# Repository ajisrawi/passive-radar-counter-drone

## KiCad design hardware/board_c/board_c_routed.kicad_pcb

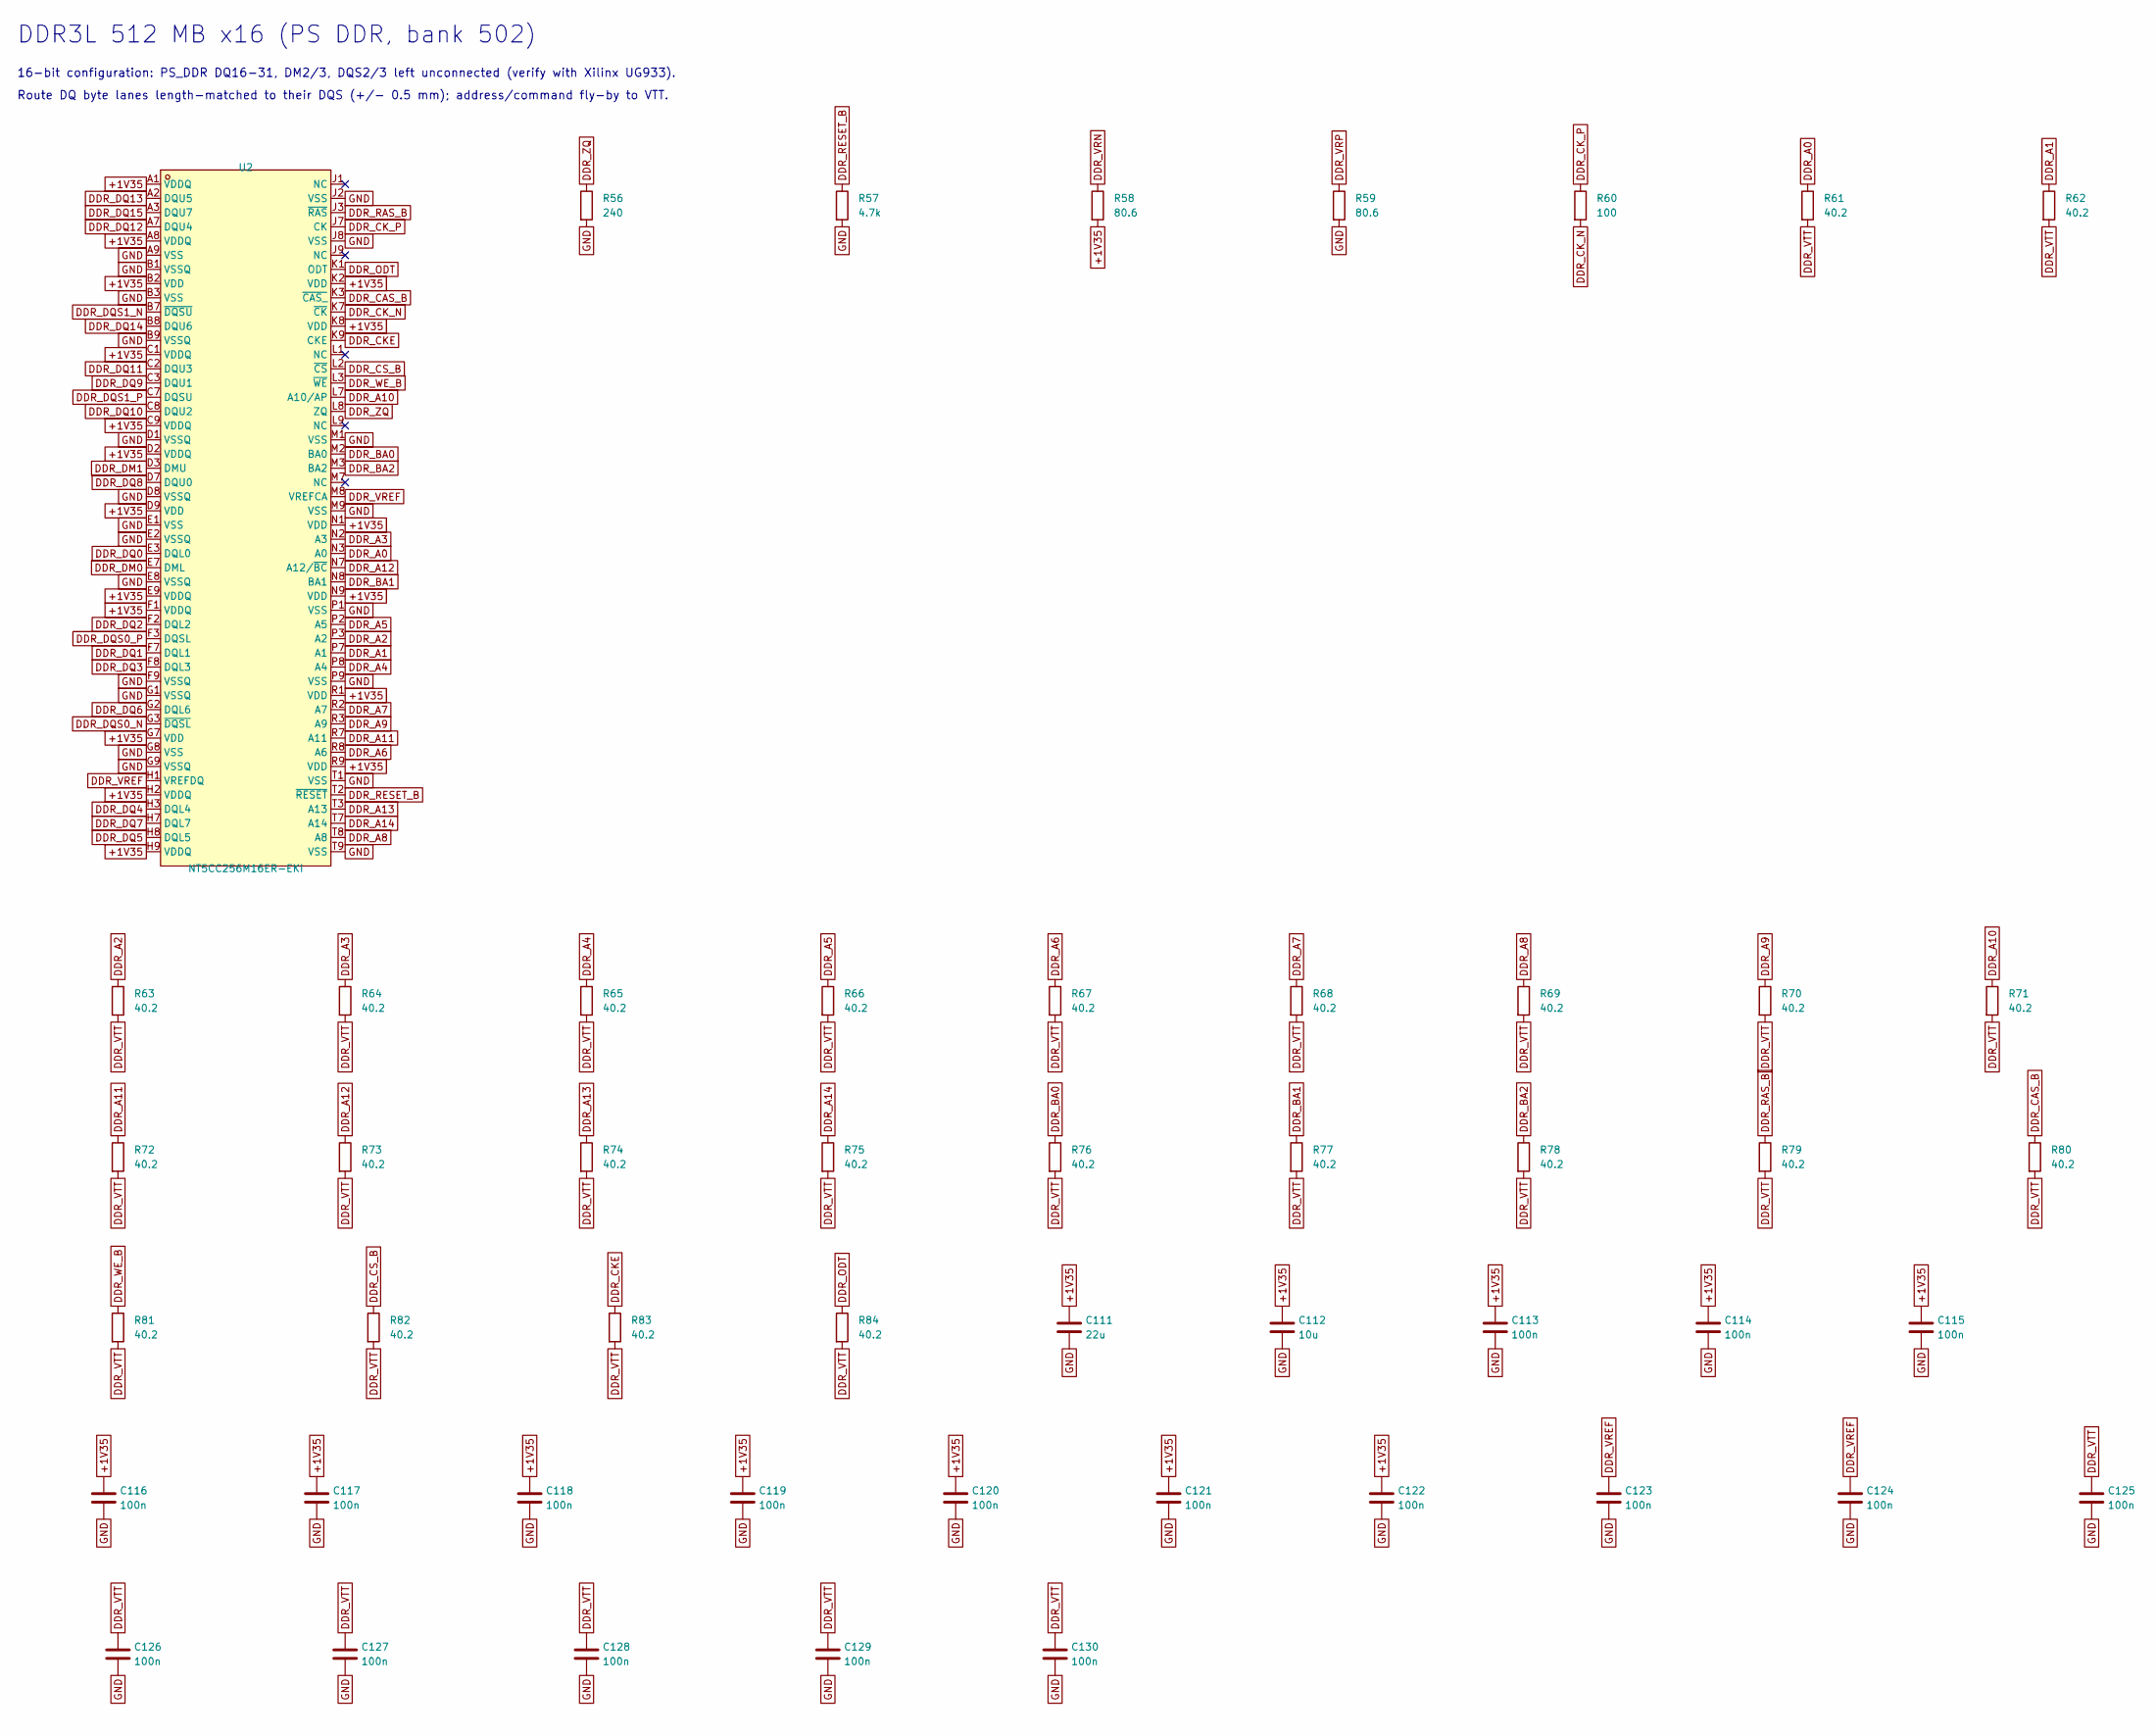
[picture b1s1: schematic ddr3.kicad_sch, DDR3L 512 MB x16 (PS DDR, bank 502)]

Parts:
C111: 22u; C_0805_2012Metric; LCSC C45783
C112: 10u; C_0603_1608Metric; LCSC C19702
C113, C114, C115, C116, C117, C118, C119, C120, C121, C122, C123, C124, C125, C126, C127, C128, C129, C130: 100n; C_0402_1005Metric; LCSC C1525
R56: 240; R_0402_1005Metric; Tolerance 1%
R57: 4.7k; R_0402_1005Metric; LCSC C25900
R58, R59: 80.6; R_0402_1005Metric; Tolerance 1%
R60: 100; R_0402_1005Metric
R61, R62, R63, R64, R65, R66, R67, R68, R69, R70, R71, R72, R73, R74, R75, R76, R77, R78, R79, R80, R81, R82, R83, R84: 40.2; R_0402_1005Metric
U2: NT5CC256M16ER-EKI; TFBGA-96_L13.0-W8.0-R16-C6-P0.80-TL; MPN NT5CC256M16ER-EKI; LCSC C2841153

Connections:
+1V35: C111.1, C112.1, C113.1, C114.1, C115.1, C116.1, C117.1, C118.1, C119.1, C120.1, C121.1, C122.1, R58.2, U2.A1 (VDDQ), U2.A8 (VDDQ), U2.B2 (VDD), U2.C1 (VDDQ), U2.C9 (VDDQ), U2.D2 (VDDQ), U2.D9 (VDD), U2.E9 (VDDQ), U2.F1 (VDDQ), U2.G7 (VDD), U2.H2 (VDDQ), U2.H9 (VDDQ), U2.K2 (VDD), U2.K8 (VDD), U2.N1 (VDD), U2.N9 (VDD), U2.R1 (VDD), U2.R9 (VDD); also elsewhere on the board
DDR_A0: R61.1, U2.N3 (A0); also elsewhere on the board
DDR_A1: R62.1, U2.P7 (A1); also elsewhere on the board
DDR_A2: R63.1, U2.P3 (A2); also elsewhere on the board
DDR_A3: R64.1, U2.N2 (A3); also elsewhere on the board
DDR_A4: R65.1, U2.P8 (A4); also elsewhere on the board
DDR_A5: R66.1, U2.P2 (A5); also elsewhere on the board
DDR_A6: R67.1, U2.R8 (A6); also elsewhere on the board
DDR_A7: R68.1, U2.R2 (A7); also elsewhere on the board
DDR_A8: R69.1, U2.T8 (A8); also elsewhere on the board
DDR_A9: R70.1, U2.R3 (A9); also elsewhere on the board
DDR_A10: R71.1, U2.L7 (A10/AP); also elsewhere on the board
DDR_A11: R72.1, U2.R7 (A11); also elsewhere on the board
DDR_A12: R73.1, U2.N7 (A12/~BC); also elsewhere on the board
DDR_A13: R74.1, U2.T3 (A13); also elsewhere on the board
DDR_A14: R75.1, U2.T7 (A14); also elsewhere on the board
DDR_BA0: R76.1, U2.M2 (BA0); also elsewhere on the board
DDR_BA1: R77.1, U2.N8 (BA1); also elsewhere on the board
DDR_BA2: R78.1, U2.M3 (BA2); also elsewhere on the board
DDR_CAS_B: R80.1, U2.K3 (~CAS_); also elsewhere on the board
DDR_CKE: R83.1, U2.K9 (CKE); also elsewhere on the board
DDR_CK_N: R60.2, U2.K7 (~CK); also elsewhere on the board
DDR_CK_P: R60.1, U2.J7 (CK); also elsewhere on the board
DDR_CS_B: R82.1, U2.L2 (~CS); also elsewhere on the board
DDR_DM0: U2.E7 (DML); also elsewhere on the board
DDR_DM1: U2.D3 (DMU); also elsewhere on the board
DDR_DQ0: U2.E3 (DQL0); also elsewhere on the board
DDR_DQ1: U2.F7 (DQL1); also elsewhere on the board
DDR_DQ2: U2.F2 (DQL2); also elsewhere on the board
DDR_DQ3: U2.F8 (DQL3); also elsewhere on the board
DDR_DQ4: U2.H3 (DQL4); also elsewhere on the board
DDR_DQ5: U2.H8 (DQL5); also elsewhere on the board
DDR_DQ6: U2.G2 (DQL6); also elsewhere on the board
DDR_DQ7: U2.H7 (DQL7); also elsewhere on the board
DDR_DQ8: U2.D7 (DQU0); also elsewhere on the board
DDR_DQ9: U2.C3 (DQU1); also elsewhere on the board
DDR_DQ10: U2.C8 (DQU2); also elsewhere on the board
DDR_DQ11: U2.C2 (DQU3); also elsewhere on the board
DDR_DQ12: U2.A7 (DQU4); also elsewhere on the board
DDR_DQ13: U2.A2 (DQU5); also elsewhere on the board
DDR_DQ14: U2.B8 (DQU6); also elsewhere on the board
DDR_DQ15: U2.A3 (DQU7); also elsewhere on the board
DDR_DQS0_N: U2.G3 (~DQSL); also elsewhere on the board
DDR_DQS0_P: U2.F3 (DQSL); also elsewhere on the board
DDR_DQS1_N: U2.B7 (~DQSU); also elsewhere on the board
DDR_DQS1_P: U2.C7 (DQSU); also elsewhere on the board
DDR_ODT: R84.1, U2.K1 (ODT); also elsewhere on the board
DDR_RAS_B: R79.1, U2.J3 (~RAS); also elsewhere on the board
DDR_RESET_B: R57.1, U2.T2 (~RESET); also elsewhere on the board
DDR_VREF: C123.1, C124.1, U2.H1 (VREFDQ), U2.M8 (VREFCA); also elsewhere on the board
DDR_VRN: R58.1; also elsewhere on the board
DDR_VRP: R59.1; also elsewhere on the board
DDR_VTT: C125.1, C126.1, C127.1, C128.1, C129.1, C130.1, R61.2, R62.2, R63.2, R64.2, R65.2, R66.2, R67.2, R68.2, R69.2, R70.2, R71.2, R72.2, R73.2, R74.2, R75.2, R76.2, R77.2, R78.2, R79.2, R80.2, R81.2, R82.2, R83.2, R84.2; also elsewhere on the board
DDR_WE_B: R81.1, U2.L3 (~WE); also elsewhere on the board
DDR_ZQ: R56.1, U2.L8 (ZQ)
GND: C111.2, C112.2, C113.2, C114.2, C115.2, C116.2, C117.2, C118.2, C119.2, C120.2, C121.2, C122.2, C123.2, C124.2, C125.2, C126.2, C127.2, C128.2, C129.2, C130.2, R56.2, R57.2, R59.2, U2.A9 (VSS), U2.B1 (VSSQ), U2.B3 (VSS), U2.B9 (VSSQ), U2.D1 (VSSQ), U2.D8 (VSSQ), U2.E1 (VSS), U2.E2 (VSSQ), U2.E8 (VSSQ), U2.F9 (VSSQ), U2.G1 (VSSQ), U2.G8 (VSS), U2.G9 (VSSQ), U2.J2 (VSS), U2.J8 (VSS), U2.M1 (VSS), U2.M9 (VSS), U2.P1 (VSS), U2.P9 (VSS), U2.T1 (VSS), U2.T9 (VSS); also elsewhere on the board

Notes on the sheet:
DDR3L 512 MB x16 (PS DDR, bank 502)
16-bit configuration: PS_DDR DQ16-31, DM2/3, DQS2/3 left unconnected (verify with Xilinx UG933).
Route DQ byte lanes length-matched to their DQS (+/- 0.5 mm); address/command fly-by to VTT.

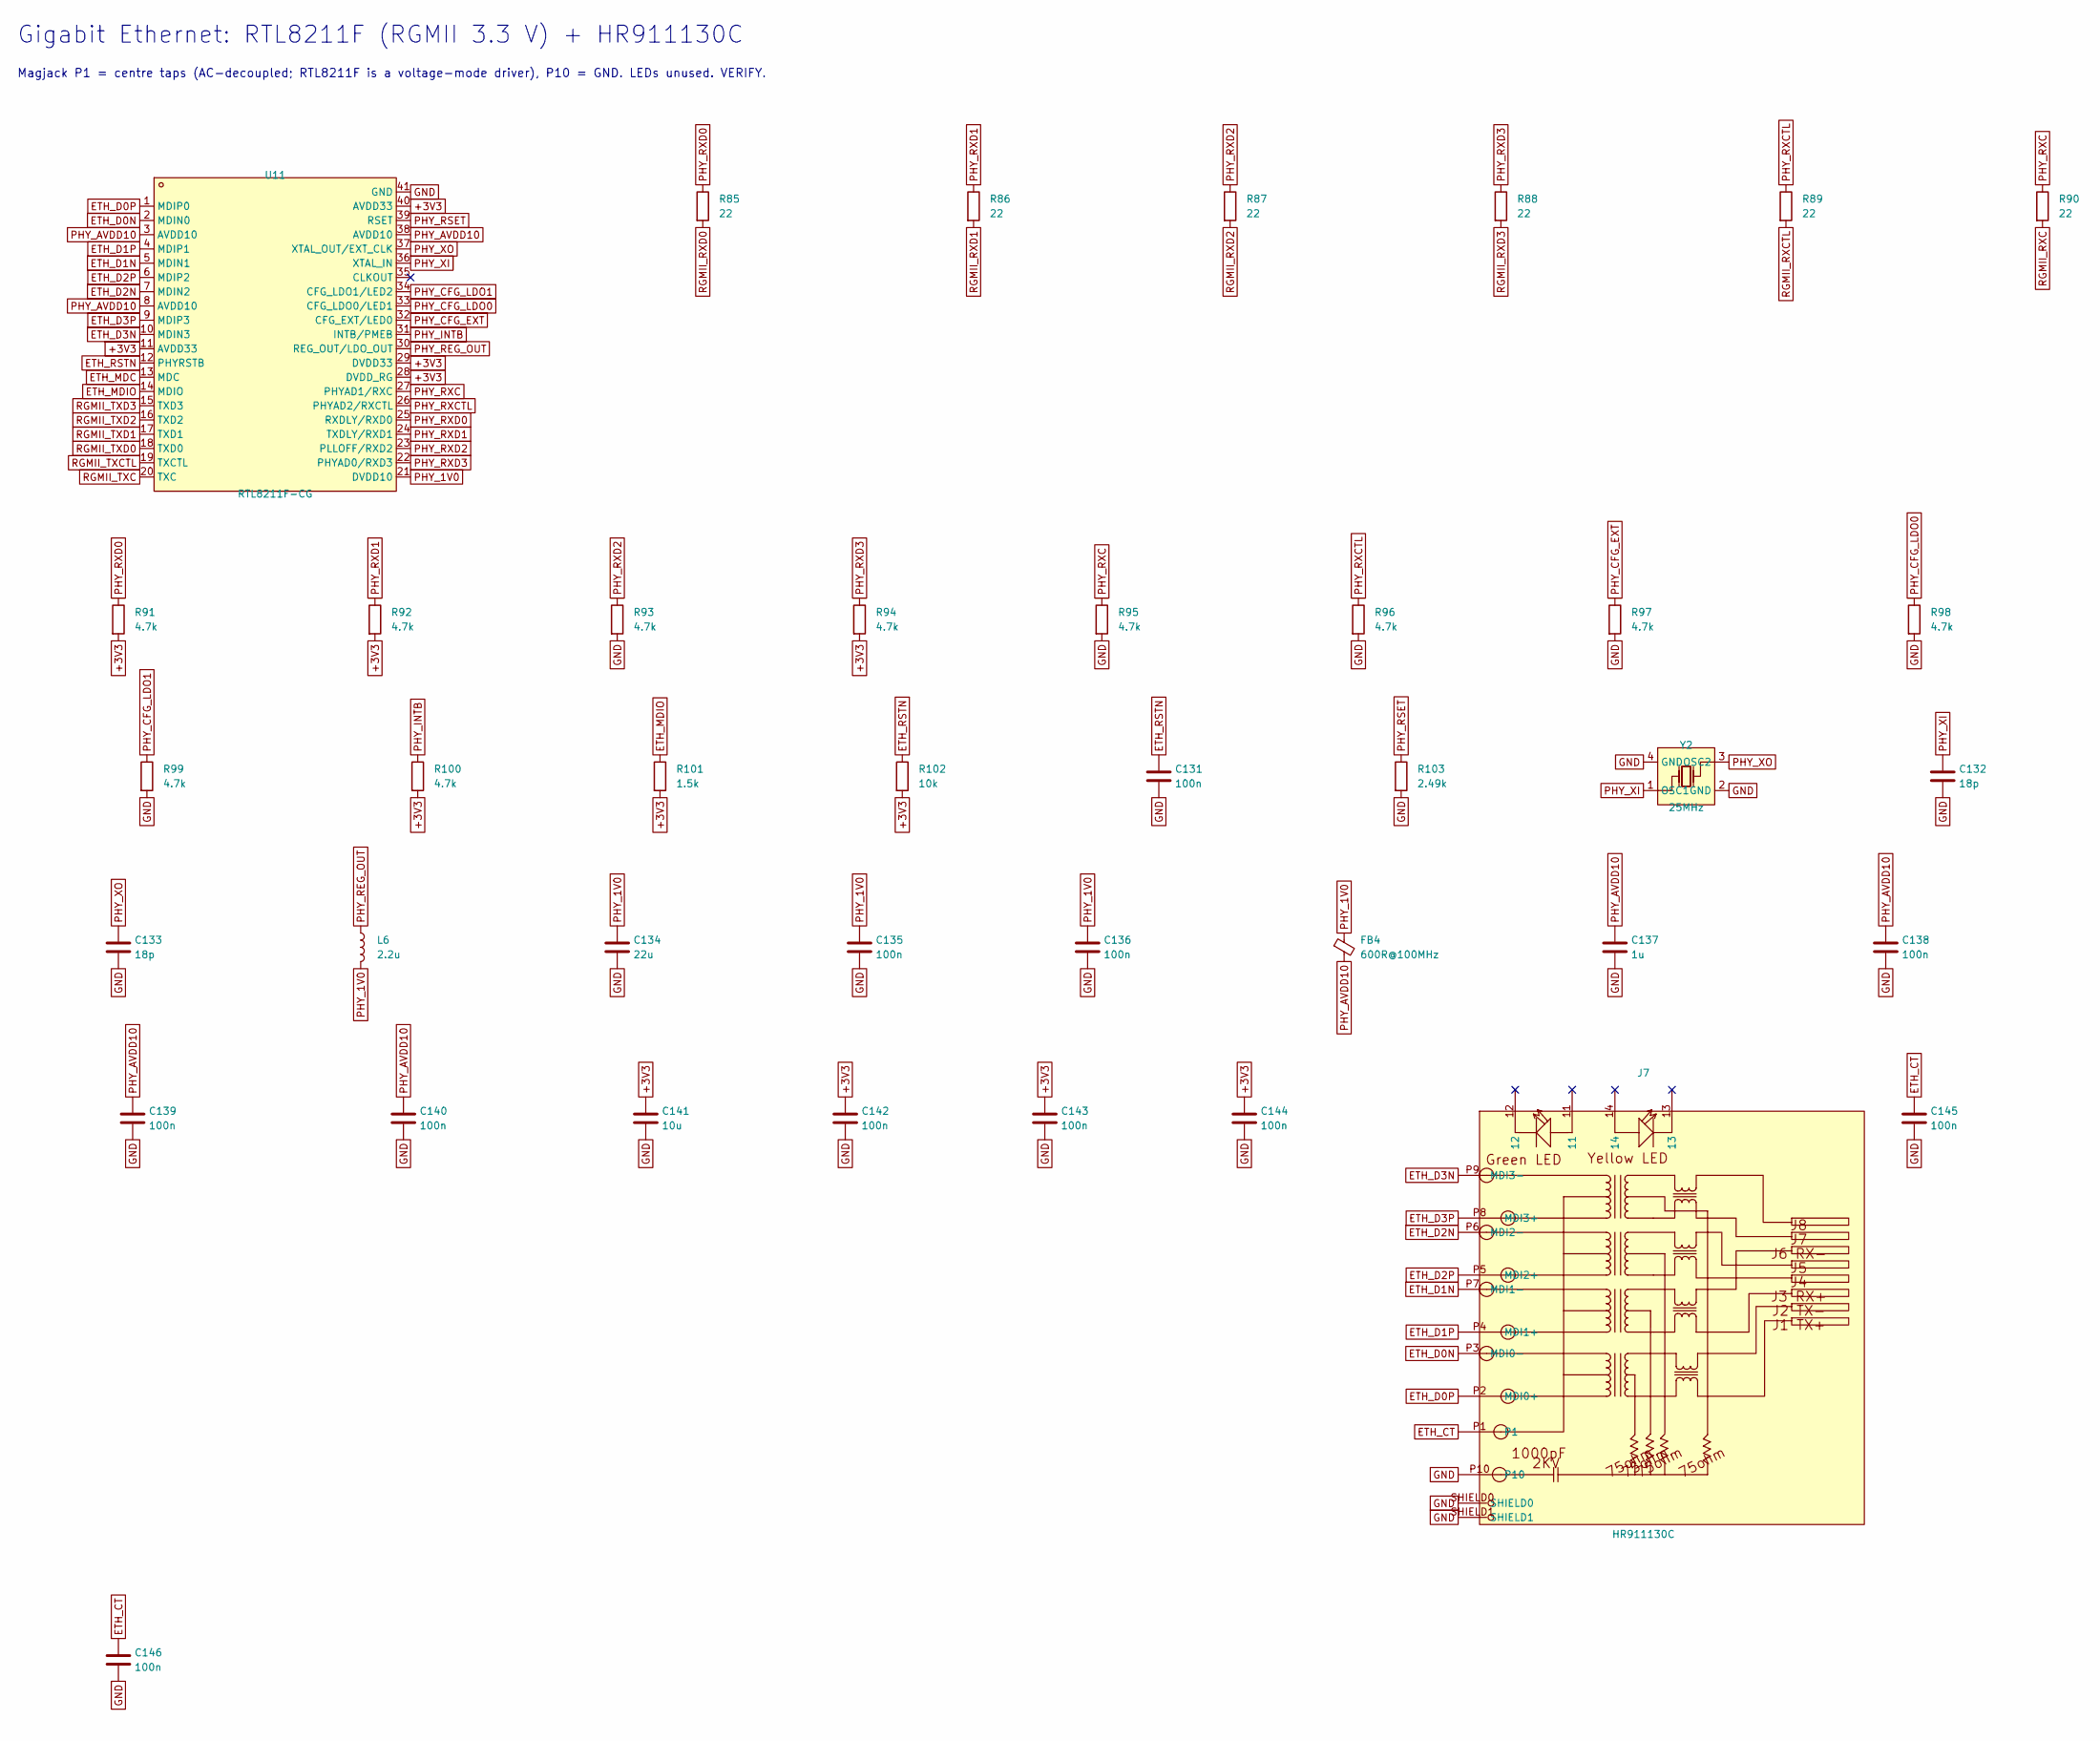
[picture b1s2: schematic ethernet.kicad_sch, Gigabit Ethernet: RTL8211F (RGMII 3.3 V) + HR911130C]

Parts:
C131, C135, C136, C138, C139, C140, C142, C143, C144, C145, C146: 100n; C_0402_1005Metric; LCSC C1525
C132, C133: 18p; C_0402_1005Metric
C134: 22u; C_0805_2012Metric; LCSC C45783
C137: 1u; C_0402_1005Metric; LCSC C52923
C141: 10u; C_0603_1608Metric; LCSC C19702
FB4: 600R@100MHz; L_0603_1608Metric
J7: HR911130C; RJ45-TH_HR911130C; MPN HR911130C; LCSC C50933
L6: 2.2u; L_0603_1608Metric
R85, R86, R87, R88, R89, R90: 22; R_0402_1005Metric
R91, R92, R93, R94, R95, R96, R97, R98, R99, R100: 4.7k; R_0402_1005Metric; LCSC C25900
R101: 1.5k; R_0402_1005Metric
R102: 10k; R_0402_1005Metric; LCSC C25744
R103: 2.49k; R_0402_1005Metric; Tolerance 1%
U11: RTL8211F-CG; WQFN-40_L5.0-W5.0-P0.4-BL-EP; MPN RTL8211F-CG; LCSC C187932
Y2: 25MHz; CRYSTAL-SMD_4P-L3.2-W2.5-BL; MPN X322525MOB4SI; LCSC C9006

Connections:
+3V3: C141.1, C142.1, C143.1, C144.1, R91.2, R92.2, R94.2, R100.2, R101.2, R102.2, U11.11 (AVDD33), U11.28 (DVDD_RG), U11.29 (DVDD33), U11.40 (AVDD33); also elsewhere on the board
ETH_CT: C145.1, C146.1, J7.P1
ETH_D0N: J7.P3 (MDI0-), U11.2 (MDIN0)
ETH_D0P: J7.P2 (MDI0+), U11.1 (MDIP0)
ETH_D1N: J7.P7 (MDI1-), U11.5 (MDIN1)
ETH_D1P: J7.P4 (MDI1+), U11.4 (MDIP1)
ETH_D2N: J7.P6 (MDI2-), U11.7 (MDIN2)
ETH_D2P: J7.P5 (MDI2+), U11.6 (MDIP2)
ETH_D3N: J7.P9 (MDI3-), U11.10 (MDIN3)
ETH_D3P: J7.P8 (MDI3+), U11.9 (MDIP3)
ETH_MDC: U11.13 (MDC); also elsewhere on the board
ETH_MDIO: R101.1, U11.14 (MDIO); also elsewhere on the board
ETH_RSTN: C131.1, R102.1, U11.12 (PHYRSTB); also elsewhere on the board
GND: C131.2, C132.2, C133.2, C134.2, C135.2, C136.2, C137.2, C138.2, C139.2, C140.2, C141.2, C142.2, C143.2, C144.2, C145.2, C146.2, J7.P10, J7.SHIELD0, J7.SHIELD1, R93.2, R95.2, R96.2, R97.2, R98.2, R99.2, R103.2, U11.41 (GND), Y2.2 (GND), Y2.4 (GND); also elsewhere on the board
PHY_1V0: C134.1, C135.1, C136.1, FB4.1, L6.2, U11.21 (DVDD10)
PHY_AVDD10: C137.1, C138.1, C139.1, C140.1, FB4.2, U11.3 (AVDD10), U11.8 (AVDD10), U11.38 (AVDD10)
PHY_CFG_EXT: R97.1, U11.32 (CFG_EXT/LED0)
PHY_CFG_LDO0: R98.1, U11.33 (CFG_LDO0/LED1)
PHY_CFG_LDO1: R99.1, U11.34 (CFG_LDO1/LED2)
PHY_INTB: R100.1, U11.31 (INTB/PMEB)
PHY_REG_OUT: L6.1, U11.30 (REG_OUT/LDO_OUT)
PHY_RSET: R103.1, U11.39 (RSET)
PHY_RXC: R90.1, R95.1, U11.27 (PHYAD1/RXC)
PHY_RXCTL: R89.1, R96.1, U11.26 (PHYAD2/RXCTL)
PHY_RXD0: R85.1, R91.1, U11.25 (RXDLY/RXD0)
PHY_RXD1: R86.1, R92.1, U11.24 (TXDLY/RXD1)
PHY_RXD2: R87.1, R93.1, U11.23 (PLLOFF/RXD2)
PHY_RXD3: R88.1, R94.1, U11.22 (PHYAD0/RXD3)
PHY_XI: C132.1, U11.36 (XTAL_IN), Y2.1 (OSC1)
PHY_XO: C133.1, U11.37 (XTAL_OUT/EXT_CLK), Y2.3 (OSC2)
RGMII_RXC: R90.2; also elsewhere on the board
RGMII_RXCTL: R89.2; also elsewhere on the board
RGMII_RXD0: R85.2; also elsewhere on the board
RGMII_RXD1: R86.2; also elsewhere on the board
RGMII_RXD2: R87.2; also elsewhere on the board
RGMII_RXD3: R88.2; also elsewhere on the board
RGMII_TXC: U11.20 (TXC); also elsewhere on the board
RGMII_TXCTL: U11.19 (TXCTL); also elsewhere on the board
RGMII_TXD0: U11.18 (TXD0); also elsewhere on the board
RGMII_TXD1: U11.17 (TXD1); also elsewhere on the board
RGMII_TXD2: U11.16 (TXD2); also elsewhere on the board
RGMII_TXD3: U11.15 (TXD3); also elsewhere on the board

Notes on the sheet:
Gigabit Ethernet: RTL8211F (RGMII 3.3 V) + HR911130C
Magjack P1 = centre taps (AC-decoupled; RTL8211F is a voltage-mode driver), P10 = GND. LEDs unused. VERIFY.

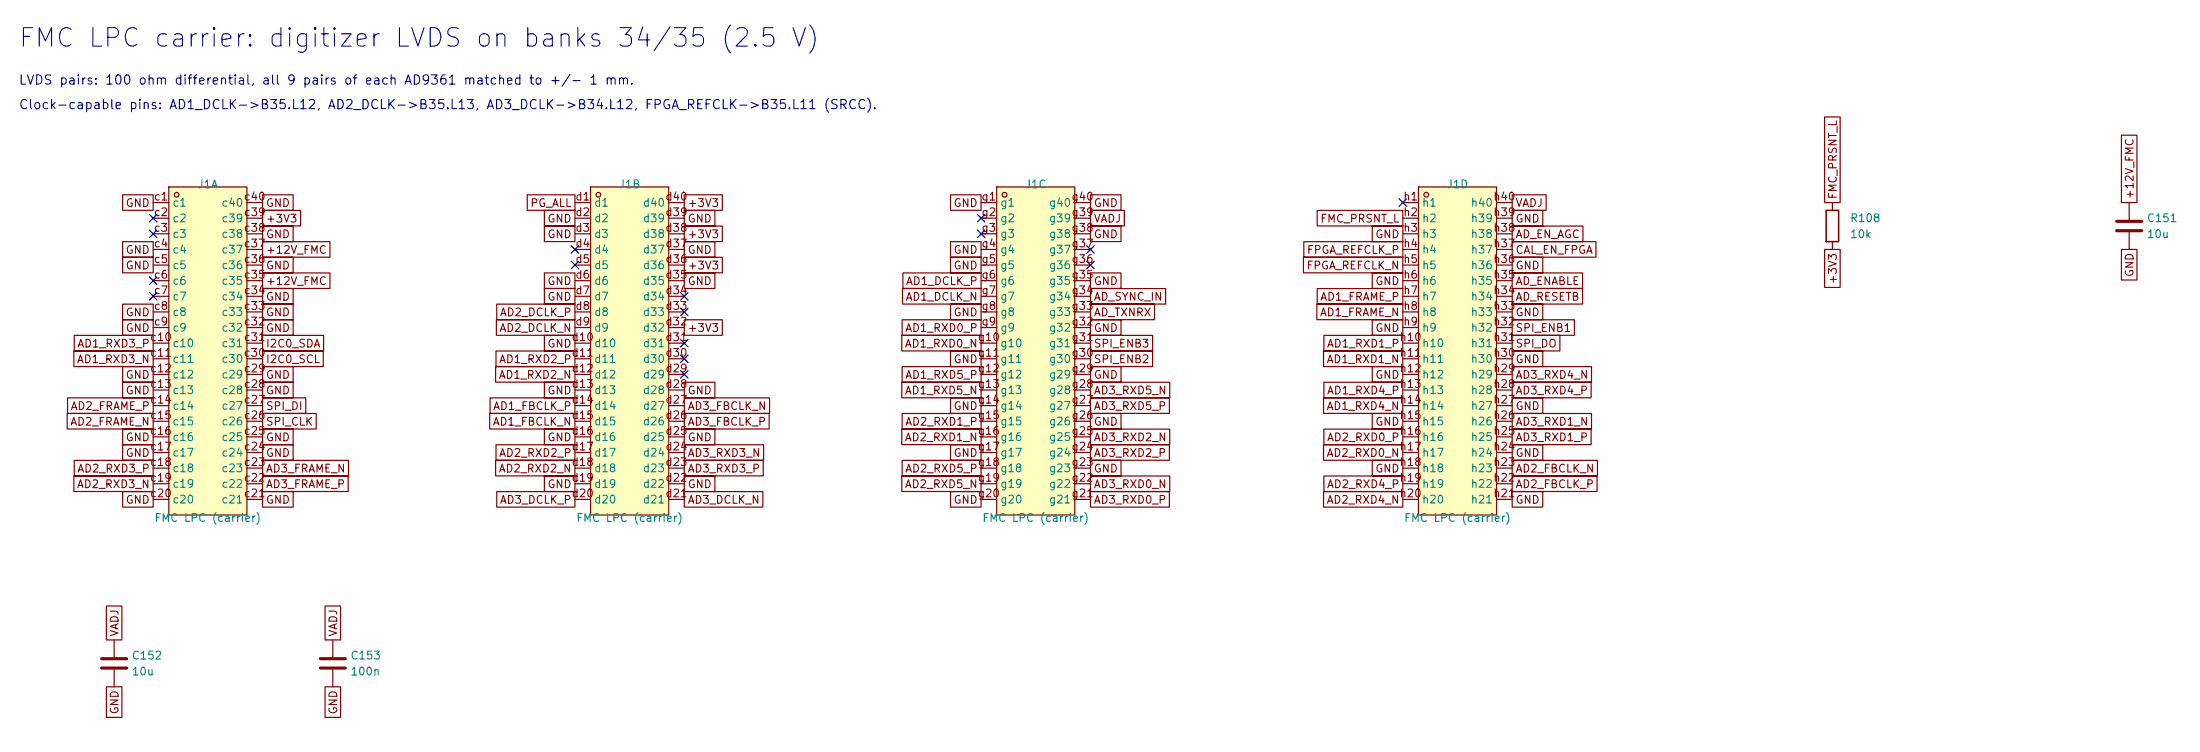
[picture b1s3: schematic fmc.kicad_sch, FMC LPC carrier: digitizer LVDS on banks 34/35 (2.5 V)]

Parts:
C151: 10u; C_0805_2012Metric
C152: 10u; C_0603_1608Metric; LCSC C19702
C153: 100n; C_0402_1005Metric; LCSC C1525
J1: FMC LPC (carrier); BGA-160_L56.6-W13.2-R4-C40-P1.27-BR; MPN ASP-134603-01; LCSC C2836665
R108: 10k; R_0402_1005Metric; LCSC C25744

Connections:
+3V3: J1.c39, J1.d32, J1.d36, J1.d38, J1.d40, R108.2; also elsewhere on the board
+12V_FMC: C151.1, J1.c35, J1.c37; also elsewhere on the board
AD1_DCLK_N: J1.g7; also elsewhere on the board
AD1_DCLK_P: J1.g6; also elsewhere on the board
AD1_FBCLK_N: J1.d15; also elsewhere on the board
AD1_FBCLK_P: J1.d14; also elsewhere on the board
AD1_FRAME_N: J1.h8; also elsewhere on the board
AD1_FRAME_P: J1.h7; also elsewhere on the board
AD1_RXD0_N: J1.g10; also elsewhere on the board
AD1_RXD0_P: J1.g9; also elsewhere on the board
AD1_RXD1_N: J1.h11; also elsewhere on the board
AD1_RXD1_P: J1.h10; also elsewhere on the board
AD1_RXD2_N: J1.d12; also elsewhere on the board
AD1_RXD2_P: J1.d11; also elsewhere on the board
AD1_RXD3_N: J1.c11; also elsewhere on the board
AD1_RXD3_P: J1.c10; also elsewhere on the board
AD1_RXD4_N: J1.h14; also elsewhere on the board
AD1_RXD4_P: J1.h13; also elsewhere on the board
AD1_RXD5_N: J1.g13; also elsewhere on the board
AD1_RXD5_P: J1.g12; also elsewhere on the board
AD2_DCLK_N: J1.d9; also elsewhere on the board
AD2_DCLK_P: J1.d8; also elsewhere on the board
AD2_FBCLK_N: J1.h23; also elsewhere on the board
AD2_FBCLK_P: J1.h22; also elsewhere on the board
AD2_FRAME_N: J1.c15; also elsewhere on the board
AD2_FRAME_P: J1.c14; also elsewhere on the board
AD2_RXD0_N: J1.h17; also elsewhere on the board
AD2_RXD0_P: J1.h16; also elsewhere on the board
AD2_RXD1_N: J1.g16; also elsewhere on the board
AD2_RXD1_P: J1.g15; also elsewhere on the board
AD2_RXD2_N: J1.d18; also elsewhere on the board
AD2_RXD2_P: J1.d17; also elsewhere on the board
AD2_RXD3_N: J1.c19; also elsewhere on the board
AD2_RXD3_P: J1.c18; also elsewhere on the board
AD2_RXD4_N: J1.h20; also elsewhere on the board
AD2_RXD4_P: J1.h19; also elsewhere on the board
AD2_RXD5_N: J1.g19; also elsewhere on the board
AD2_RXD5_P: J1.g18; also elsewhere on the board
AD3_DCLK_N: J1.d21; also elsewhere on the board
AD3_DCLK_P: J1.d20; also elsewhere on the board
AD3_FBCLK_N: J1.d27; also elsewhere on the board
AD3_FBCLK_P: J1.d26; also elsewhere on the board
AD3_FRAME_N: J1.c23; also elsewhere on the board
AD3_FRAME_P: J1.c22; also elsewhere on the board
AD3_RXD0_N: J1.g22; also elsewhere on the board
AD3_RXD0_P: J1.g21; also elsewhere on the board
AD3_RXD1_N: J1.h26; also elsewhere on the board
AD3_RXD1_P: J1.h25; also elsewhere on the board
AD3_RXD2_N: J1.g25; also elsewhere on the board
AD3_RXD2_P: J1.g24; also elsewhere on the board
AD3_RXD3_N: J1.d24; also elsewhere on the board
AD3_RXD3_P: J1.d23; also elsewhere on the board
AD3_RXD4_N: J1.h29; also elsewhere on the board
AD3_RXD4_P: J1.h28; also elsewhere on the board
AD3_RXD5_N: J1.g28; also elsewhere on the board
AD3_RXD5_P: J1.g27; also elsewhere on the board
AD_ENABLE: J1.h35; also elsewhere on the board
AD_EN_AGC: J1.h38; also elsewhere on the board
AD_RESETB: J1.h34; also elsewhere on the board
AD_SYNC_IN: J1.g34; also elsewhere on the board
AD_TXNRX: J1.g33; also elsewhere on the board
CAL_EN_FPGA: J1.h37; also elsewhere on the board
FMC_PRSNT_L: J1.h2, R108.1; also elsewhere on the board
FPGA_REFCLK_N: J1.h5; also elsewhere on the board
FPGA_REFCLK_P: J1.h4; also elsewhere on the board
GND: C151.2, C152.2, C153.2, J1.c1, J1.c4, J1.c5, J1.c8, J1.c9, J1.c12, J1.c13, J1.c16, J1.c17, J1.c20, J1.c21, J1.c24, J1.c25, J1.c28, J1.c29, J1.c32, J1.c33, J1.c34, J1.c36, J1.c38, J1.c40, J1.d2, J1.d3, J1.d6, J1.d7, J1.d10, J1.d13, J1.d16, J1.d19, J1.d22, J1.d25, J1.d28, J1.d35, J1.d37, J1.d39, J1.g1, J1.g4, J1.g5, J1.g8, J1.g11, J1.g14, J1.g17, J1.g20, J1.g23, J1.g26, J1.g29, J1.g32, J1.g35, J1.g38, J1.g40, J1.h3, J1.h6, J1.h9, J1.h12, J1.h15, J1.h18, J1.h21, J1.h24, J1.h27, J1.h30, J1.h33, J1.h36, J1.h39; also elsewhere on the board
I2C0_SCL: J1.c30; also elsewhere on the board
I2C0_SDA: J1.c31; also elsewhere on the board
PG_ALL: J1.d1; also elsewhere on the board
SPI_CLK: J1.c26; also elsewhere on the board
SPI_DI: J1.c27; also elsewhere on the board
SPI_DO: J1.h31; also elsewhere on the board
SPI_ENB1: J1.h32; also elsewhere on the board
SPI_ENB2: J1.g30; also elsewhere on the board
SPI_ENB3: J1.g31; also elsewhere on the board
VADJ: C152.1, C153.1, J1.g39, J1.h40; also elsewhere on the board

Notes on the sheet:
FMC LPC carrier: digitizer LVDS on banks 34/35 (2.5 V)
LVDS pairs: 100 ohm differential, all 9 pairs of each AD9361 matched to +/- 1 mm.
Clock-capable pins: AD1_DCLK->B35.L12, AD2_DCLK->B35.L13, AD3_DCLK->B34.L12, FPGA_REFCLK->B35.L11 (SRCC).

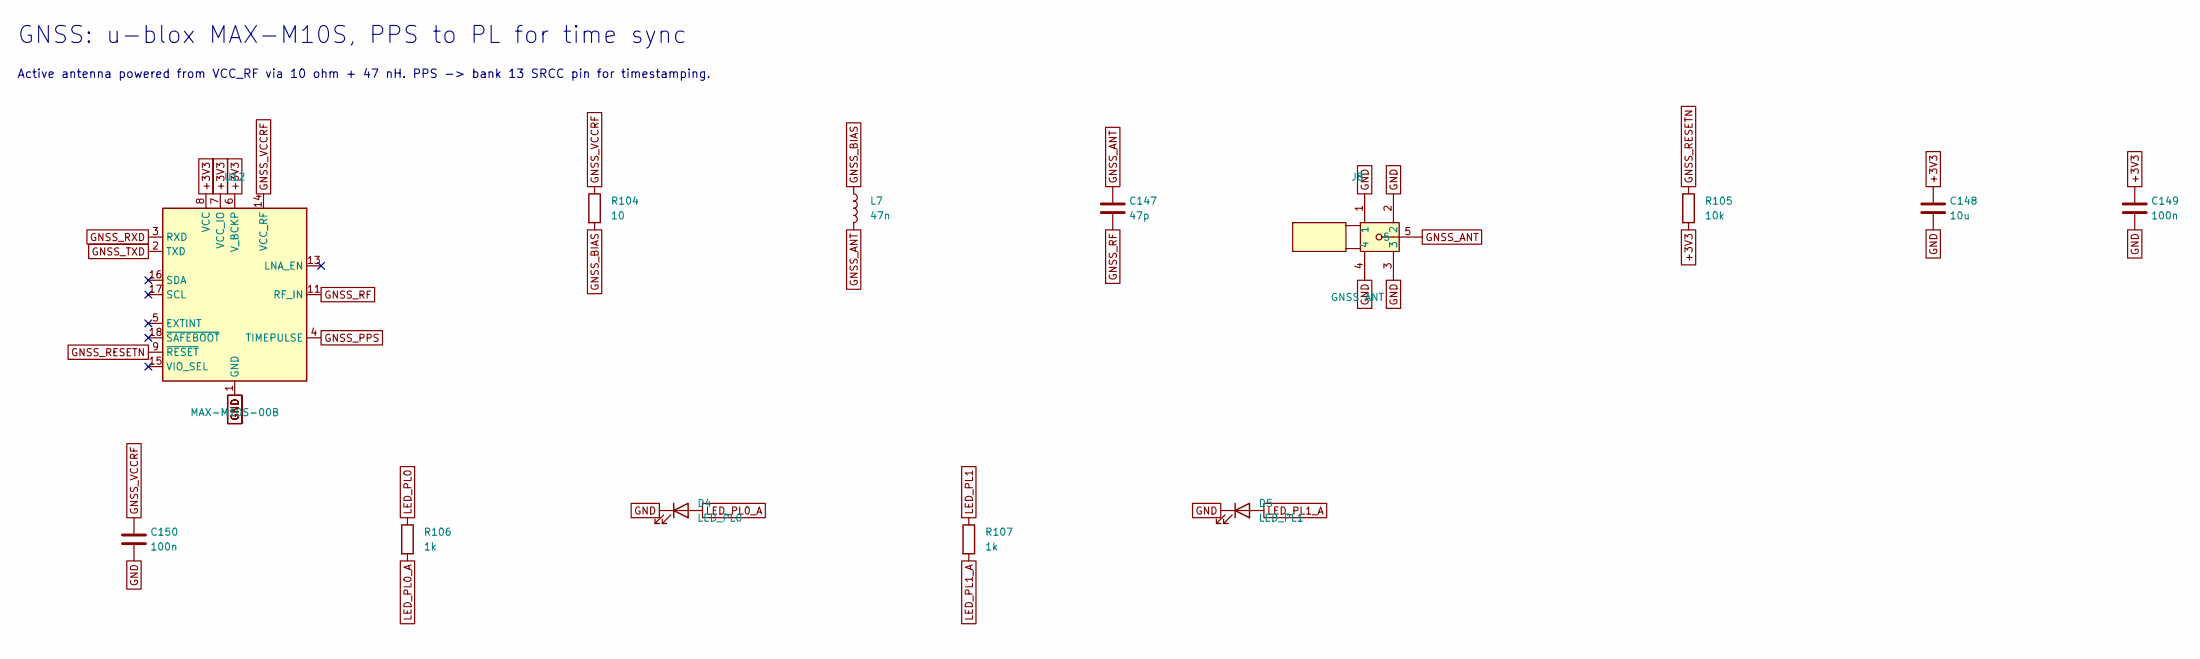
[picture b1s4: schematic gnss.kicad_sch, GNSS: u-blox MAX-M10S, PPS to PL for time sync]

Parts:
C147: 47p; C_0402_1005Metric
C148: 10u; C_0603_1608Metric; LCSC C19702
C149, C150: 100n; C_0402_1005Metric; LCSC C1525
D4: LED_PL0; LED_0603_1608Metric
D5: LED_PL1; LED_0603_1608Metric
J8: GNSS ANT; SMA-TH_BWSMA-KE-Z001; MPN BWSMA-KE-Z001; LCSC C496549
L7: 47n; L_0402_1005Metric
R104: 10; R_0402_1005Metric
R105: 10k; R_0402_1005Metric; LCSC C25744
R106, R107: 1k; R_0402_1005Metric; LCSC C11702
U12: MAX-M10S-00B; ublox_MAX; LCSC C4153167

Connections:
+3V3: C148.1, C149.1, R105.2, U12.6 (V_BCKP), U12.7 (VCC_IO), U12.8 (VCC); also elsewhere on the board
GND: C148.2, C149.2, C150.2, D4.1 (K), D5.1 (K), J8.1, J8.2, J8.3, J8.4, U12.1 (GND), U12.10 (GND), U12.12 (GND); also elsewhere on the board
GNSS_ANT: C147.1, J8.5, L7.2
GNSS_BIAS: L7.1, R104.2
GNSS_PPS: U12.4 (TIMEPULSE); also elsewhere on the board
GNSS_RESETN: R105.1, U12.9 (~RESET); also elsewhere on the board
GNSS_RF: C147.2, U12.11 (RF_IN)
GNSS_RXD: U12.3 (RXD); also elsewhere on the board
GNSS_TXD: U12.2 (TXD); also elsewhere on the board
GNSS_VCCRF: C150.1, R104.1, U12.14 (VCC_RF)
LED_PL0: R106.1; also elsewhere on the board
LED_PL0_A: D4.2 (A), R106.2
LED_PL1: R107.1; also elsewhere on the board
LED_PL1_A: D5.2 (A), R107.2

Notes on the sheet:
GNSS: u-blox MAX-M10S, PPS to PL for time sync
Active antenna powered from VCC_RF via 10 ohm + 47 nH. PPS -> bank 13 SRCC pin for timestamping.
